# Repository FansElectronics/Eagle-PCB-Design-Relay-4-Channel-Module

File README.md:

# Eagle-PCB-Design-Relay-4-Channel-Module
Desain PCB Eagle Relay 4 ChannelModule

This module active LOW
# www.FansElectronics.com

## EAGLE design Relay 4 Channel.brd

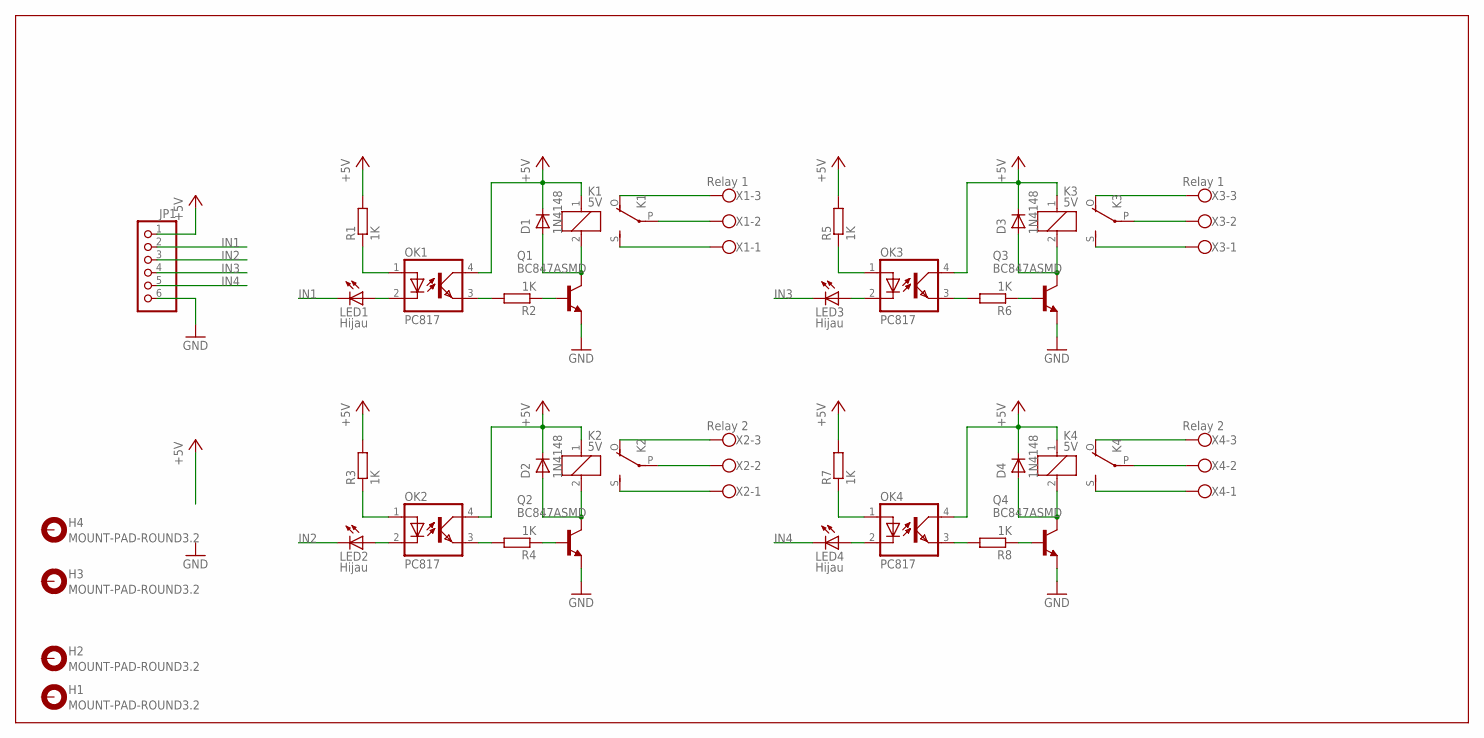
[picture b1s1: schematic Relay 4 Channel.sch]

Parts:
D1, D2, D3, D4: 1N4148; SMA-DO214AC
H1, H2, H3, H4: MOUNT-PAD-ROUND3.2; 3,2-PAD
JP1: PINHD-1X6; 1X06
K1, K2, K3, K4: 5V; ZF112
LED1, LED2, LED3, LED4: Hijau; LED3MM
OK1, OK2, OK3, OK4: PC817; DIL04
Q1, Q2, Q3, Q4: BC847ASMD; SOT23
R1, R2, R3, R4, R5, R6, R7, R8: 1K; R1206
X1, X3: Relay 1; W237-103
X2, X4: Relay 2; W237-103

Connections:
+5V: D1.K (C), D2.K (C), D3.K (C), D4.K (C), JP1.1, K1.1, K2.1, K3.1, K4.1, OK1.4 (COL), OK2.4 (COL), OK3.4 (COL), OK4.4 (COL), R1.2, R3.2, R5.2, R7.2
GND: JP1.6, Q1.2 (E), Q2.2 (E), Q3.2 (E), Q4.2 (E)
IN1: JP1.2, LED1.K (C)
IN2: JP1.3, LED2.K (C)
IN3: JP1.4, LED3.K (C)
IN4: JP1.5, LED4.K (C)
unnamed: LED1.A, OK1.2 (C)
unnamed: K1.O, X1.3
unnamed: K1.P, X1.2
unnamed: K1.S, X1.1
unnamed: OK1.1 (A), R1.1
unnamed: LED3.A, OK3.2 (C)
unnamed: OK1.3 (EMIT), R2.2
unnamed: D1.A, K1.2, Q1.3 (C)
unnamed: Q1.1 (B), R2.1
unnamed: LED2.A, OK2.2 (C)
unnamed: K2.O, X2.3
unnamed: K2.P, X2.2
unnamed: K2.S, X2.1
unnamed: OK2.1 (A), R3.1
unnamed: K3.O, X3.3
unnamed: OK2.3 (EMIT), R4.2
unnamed: D2.A, K2.2, Q2.3 (C)
unnamed: Q2.1 (B), R4.1
unnamed: K3.P, X3.2
unnamed: K3.S, X3.1
unnamed: OK3.1 (A), R5.1
unnamed: OK3.3 (EMIT), R6.2
unnamed: D3.A, K3.2, Q3.3 (C)
unnamed: Q3.1 (B), R6.1
unnamed: LED4.A, OK4.2 (C)
unnamed: K4.O, X4.3
unnamed: K4.P, X4.2
unnamed: K4.S, X4.1
unnamed: OK4.1 (A), R7.1
unnamed: OK4.3 (EMIT), R8.2
unnamed: D4.A, K4.2, Q4.3 (C)
unnamed: Q4.1 (B), R8.1

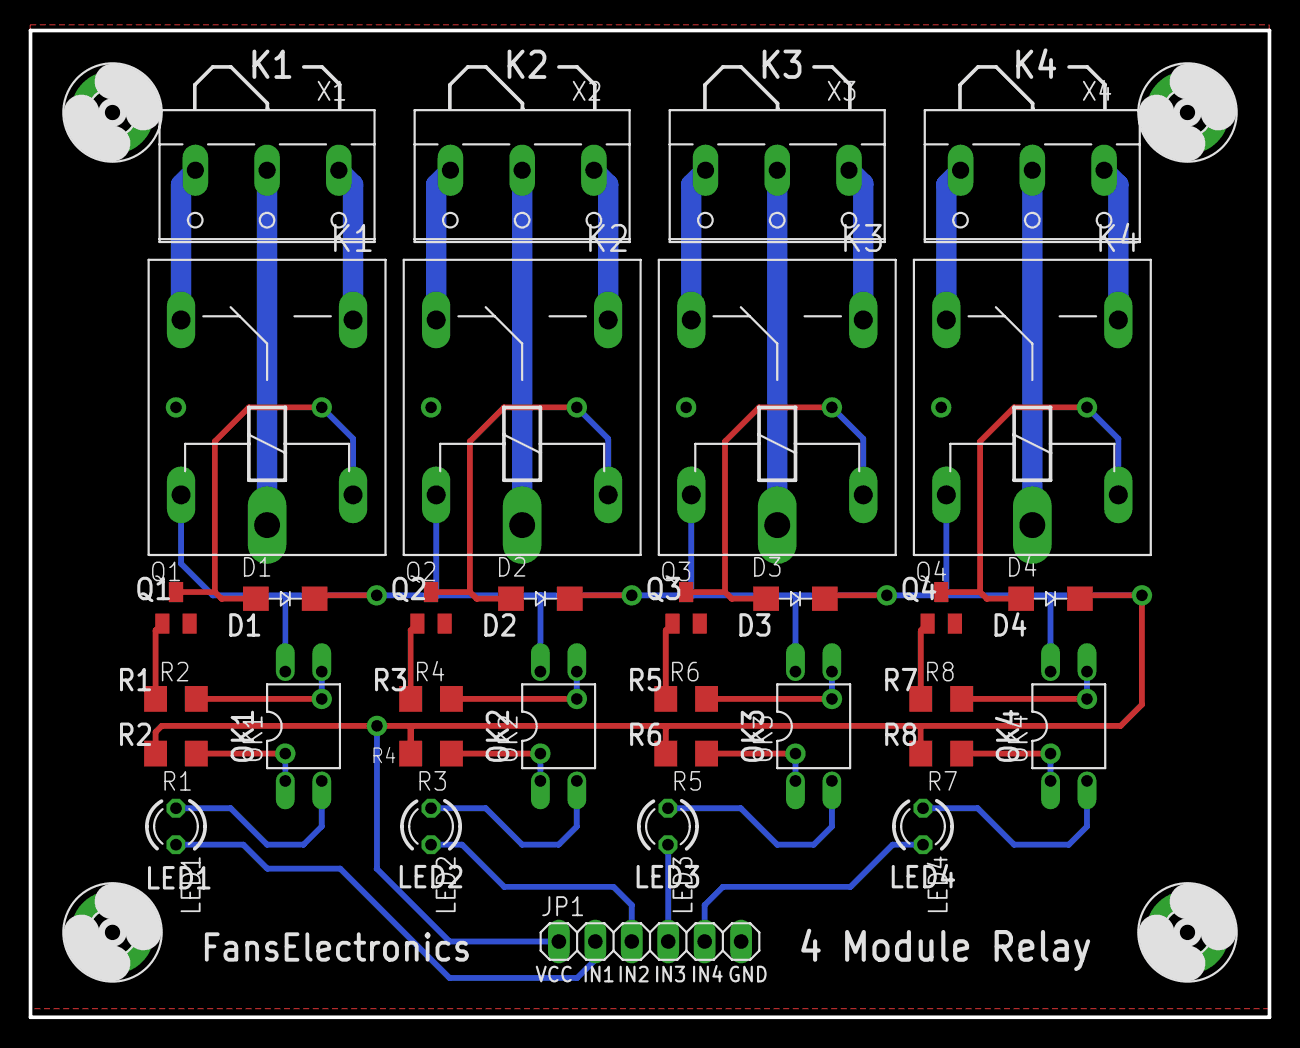
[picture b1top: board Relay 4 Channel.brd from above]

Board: 2 copper layers, 86.4 x 68.8 mm, 37 parts (0 on the bottom side), 38 nets.
